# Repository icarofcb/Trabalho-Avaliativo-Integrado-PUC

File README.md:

# Trabalho-Avaliativo-Integrado-PUC
Um repositorio para o meu trabalho avaliativo integrado de eletrônica da PUC, matéria ministrada pelo professor PJ(Paulo José)

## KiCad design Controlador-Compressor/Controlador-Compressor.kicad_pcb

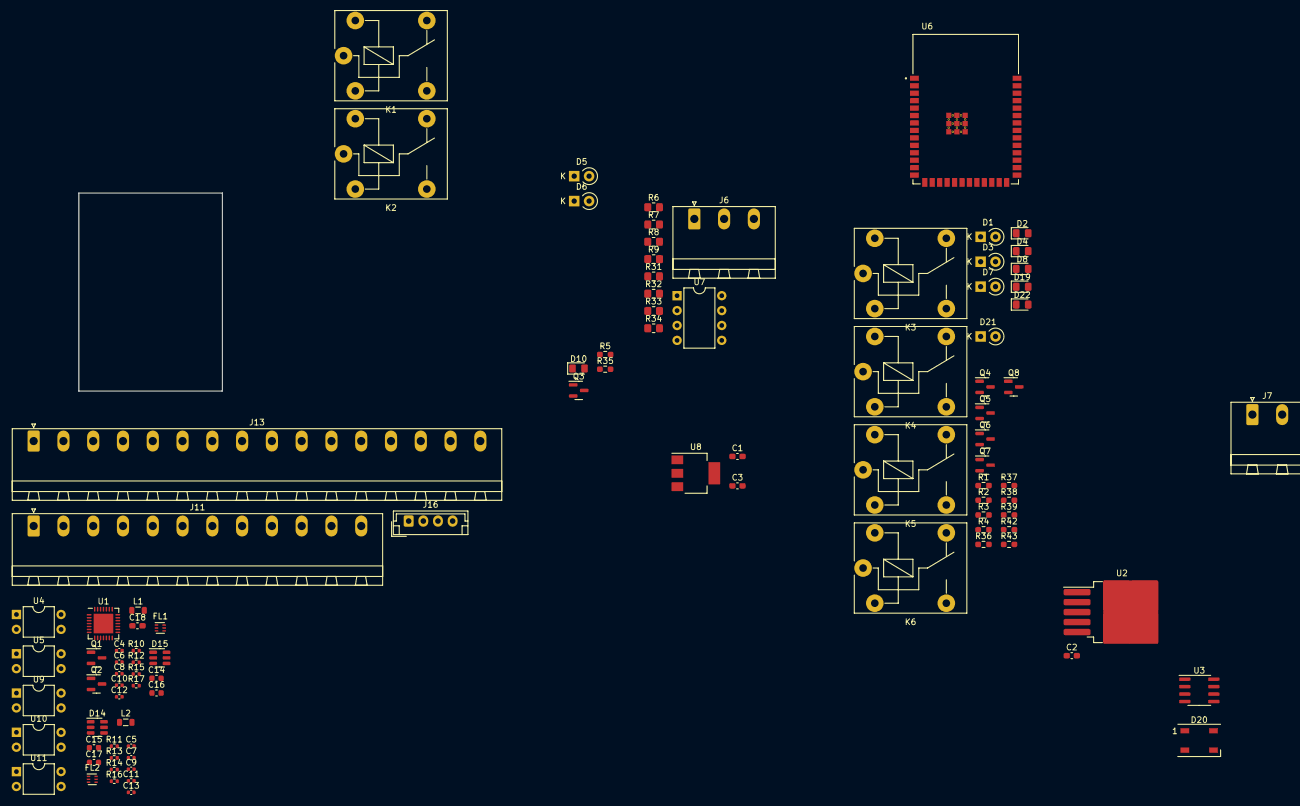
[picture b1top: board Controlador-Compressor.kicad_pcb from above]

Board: 2 copper layers, 95 parts (0 on the bottom side), 86 nets, no tracks yet.

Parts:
C1, C3, C18: 10uF; C_0603_1608Metric_Pad1.08x0.95mm_HandSolder
C2: 1uF; C_0603_1608Metric_Pad1.08x0.95mm_HandSolder
C4, C5, C8, C9: 1.5pF; C_0402_1005Metric
C6, C7, C10, C11, C12, C13: 220nF; C_0402_1005Metric
C14, C15, C16, C17: 10uF; C_0603_1608Metric
D1, D3, D5, D6, D7, D21: D; D_A-405_P2.54mm_Vertical_KathodeUp
D2, D4, D8, D10, D19, D22: LED; LED_0805_2012Metric_Pad1.15x1.40mm_HandSolder
D14, D15: SRV05-4-P-T7; SOT-23-6
D20: WS2812B; LED_WS2812B_PLCC4_5.0x5.0mm_P3.2mm
FL1, FL2: ECMF02; ST_UQFN-6L_1.5x1.7mm_Pitch0.5mm
J6: Analogico; PhoenixContact_MSTBA_2,5_3-G-5,08_1x03_P5.08mm_Horizontal
J7: Alimentação; PhoenixContact_MSTBA_2,5_2-G-5,08_1x02_P5.08mm_Horizontal
J11: Saídas Relé; PhoenixContact_MSTBA_2,5_12-G-5,08_1x12_P5.08mm_Horizontal
J13: Analógico; PhoenixContact_MSTBA_2,5_16-G-5,08_1x16_P5.08mm_Horizontal
J16: Nextion; JST_EH_B4B-EH-A_1x04_P2.50mm_Vertical
K1, K2, K3, K4, K5, K6: FINDER-36.11; Relay_SPDT_Finder_36.11
L1, L2: FBMJ2125HS420-T; L_0805_2012Metric
Q1, Q2, Q3, Q4, Q5, Q6, Q7, Q8: BC817; SOT-23
R1, R2, R3, R4, R5, R35, R36, R37, R38, R39, R42, R43: 1k; R_0603_1608Metric_Pad0.98x0.95mm_HandSolder
R6, R7: 3.3k; R_0805_2012Metric_Pad1.20x1.40mm_HandSolder
R8, R9: 10k; R_0805_2012Metric_Pad1.20x1.40mm_HandSolder
R10, R11, R12, R13: 100k; R_0402_1005Metric
R14, R15, R16, R17: 5.1K; R_0402_1005Metric
R31, R32: 33k; R_0805_2012Metric_Pad1.20x1.40mm_HandSolder
R33, R34: 100k; R_0805_2012Metric_Pad1.20x1.40mm_HandSolder
U1: CP2102N-Axx-xQFN28; QFN-28-1EP_5x5mm_P0.5mm_EP3.35x3.35mm
U2: LM2596S-5; TO-263-5_TabPin3
U3: SN75176ADR; SOIC-8_3.9x4.9mm_P1.27mm
U4, U5, U9, U10, U11: PC817; DIP-4_W7.62mm
U6: ESP32S3WROOM1N8R8; XCVR_ESP32S3WROOM1N8R8
U7: LM358; DIP-8_W7.62mm
U8: AMS1117-3.3; SOT-223-3_TabPin2

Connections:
+3V3: C2.1, C3.1, C18.1, D20.1 (VDD), U1.6 (VDD), U1.7 (VREGIN), U6.2 (3V3), U8.2 (VO)
+5V: C1.1, J16.1, U3.8 (VCC), U8.3 (VI)
+24V: D1.1 (K), D3.1 (K), D5.1 (K), D6.1 (K), D7.1 (K), D21.1 (K), J7.1, K1.A1, K2.A1, K3.A1, K4.A1, K5.A1, K6.A1, U2.1 (VIN), U7.8 (V+)
/Circuito Analógico/0_10V_FB_1: R31.2, R33.2
/Circuito Analógico/0_10V_FB_2: R32.2, R34.2
/Circuito Analógico/0_10V_OUT1: J6.1, R31.1
/Circuito Analógico/0_10V_OUT2: J6.2, R32.1
/Circuito digital/COM0: J11.2, K1.11
/Circuito digital/COM1: J11.4, K2.11
/Circuito digital/COM2: J11.6, K3.11
/Circuito digital/COM3: J11.8, K4.11
/Circuito digital/COM4: J11.10, K5.11
/Circuito digital/COM5: J11.12, K6.11
/Circuito digital/DI0: U4.4, U6.30 (IO37)
/Circuito digital/DI1: U5.4, U6.34 (IO41)
/Circuito digital/DI2: U6.35 (IO42), U9.4
/Circuito digital/DI3: U6.24 (IO47), U10.4
/Circuito digital/DI4: U6.25 (IO48), U11.4
/Circuito digital/DO0: J11.1, K1.14
/Circuito digital/DO1: J11.3, K2.14
/Circuito digital/DO2: J11.5, K3.14
/Circuito digital/DO3: J11.7, K4.14
/Circuito digital/DO4: J11.9, K5.14
/Circuito digital/DO5: J11.11, K6.14
/Circuito digital/RELE 1: R5.1, U6.19 (IO11)
/Circuito digital/RELE 2: R1.2, U6.20 (IO12)
/Circuito digital/RELE 3: R2.1, U6.21 (IO13)
/Circuito digital/RELE 4: R4.1, U6.22 (IO14)
/Circuito digital/RELE 5: R38.1, U6.8 (IO15)
/Circuito digital/RELE 6: R42.1, U6.9 (IO16)
/ESP32-S3/DE: U3.2 (~RE), U3.3 (DE), U6.29 (IO36)
/ESP32-S3/GPIO38: D20.4 (DIN), U6.31 (IO38)
/ESP32-S3/RS485_RX: U3.1 (R), U6.23 (IO21)
/ESP32-S3/RS485_TX: U3.4 (D), U6.28 (IO35)
/ESP32-S3/RX-Nextion: J16.2, U6.10 (IO17)
/ESP32-S3/RXD0: U1.25 (RXD), U6.36 (RXD0)
/ESP32-S3/TXD0: U1.26 (TXD), U6.37 (TXD0)
/ESP32-S3/Tx-Nextion: J16.3, U6.11 (IO18)
/USB->OTG/ESP_D+: D14.6 (I/O_4), FL2.1 (D+)
/USB->OTG/ESP_D-: D14.4 (I/O_3), FL2.2 (D-)
/USB->OTG/ESP_SHIELD: D14.1 (I/O_1), R11.2, R13.2
/USB->OTG/ESP_VBUS_5V: C7.1, L2.1
/USB->OTG/GPIO19: FL2.5 (D-), U6.13 (IO19)
/USB->OTG/GPIO20: FL2.6 (D+), U6.14 (IO20)
/USB->UART/D+: D15.6 (I/O_4), FL1.1 (D+)
/USB->UART/D-: D15.4 (I/O_3), FL1.2 (D-)
/USB->UART/DTR: Q2.2 (E), U1.28 (~DTR)
/USB->UART/RTS: Q1.2 (E), U1.24 (~RTS)
/USB->UART/SHIELD: D15.1 (I/O_1), R10.2, R12.2
/USB->UART/USB_D+: FL1.6 (D+), U1.4 (D+)
/USB->UART/USB_D-: FL1.5 (D-), U1.5 (D-)
/USB->UART/VBUS_5V: C6.1, D15.5 (VP), L1.1
GND: C1.2, C2.2, C3.2, C4.1, C5.1, C6.2, C7.2, C8.1, C9.1, C10.2, C11.2, C12.2, C13.2, C14.2, C15.2, C16.2, C17.2, C18.2, D14.2 (GND), D15.2 (GND), D20.3 (VSS), FL1.3 (GND), FL2.3 (GND), J6.3, J7.2, J16.4, Q3.2 (E), Q4.2 (E), Q5.2 (E), Q6.2 (E), Q7.2 (E), Q8.2 (E), R6.1, R7.1, R14.2, R15.2, R16.2, R17.2, R33.1, R34.1, U1.3 (GND), U1.29 (GND), U2.3 (GND), U2.5 (~ON/OFF), U3.5 (GND), U4.2, U4.3, U5.2, U5.3, U6.1 (GND), U6.40 (GND), U6.41_1 (GND), U6.41_2 (GND), U6.41_3 (GND), U6.41_4 (GND), U6.41_5 (GND), U6.41_6 (GND), U6.41_7 (GND), U6.41_8 (GND), U6.41_9 (GND), U7.4 (V-), U8.1 (GND), U9.2, U9.3, U10.2, U10.3, U11.2, U11.3
unnamed: C4.2, R10.1
unnamed: C5.2, R11.1
unnamed: C8.2, R12.1
unnamed: C9.2, R13.1
unnamed: D1.2 (A), D2.2 (A), K3.A2
unnamed: D2.1 (K), R3.2
unnamed: D3.2 (A), D4.2 (A), K4.A2
unnamed: D4.1 (K), R37.2
unnamed: D7.2 (A), D8.2 (A), K5.A2
unnamed: D8.1 (K), R39.2
unnamed: D5.2 (A), D10.2 (A), K1.A2
unnamed: D10.1 (K), R35.2
unnamed: D6.2 (A), D19.2 (A), K2.A2
unnamed: D19.1 (K), R36.2
unnamed: D21.2 (A), D22.2 (A), K6.A2
unnamed: D22.1 (K), R43.2
unnamed: R8.2, U7.1
unnamed: R9.2, U7.7
unnamed: Q3.1 (B), R5.2
unnamed: Q3.3 (C), R35.1
unnamed: Q4.1 (B), R1.1
unnamed: Q4.3 (C), R36.1
unnamed: Q5.1 (B), R2.2
unnamed: Q5.3 (C), R3.1
unnamed: Q6.1 (B), R4.2
unnamed: Q6.3 (C), R37.1
unnamed: Q7.1 (B), R38.2
unnamed: Q7.3 (C), R39.1
unnamed: Q8.1 (B), R42.2
unnamed: Q8.3 (C), R43.1
unnamed: R6.2, R8.1, U7.2 (-)
unnamed: R7.2, R9.1, U7.6 (-)
VBUS: C10.1, C11.1, C12.1, C13.1, C14.1, C15.1, C16.1, C17.1, L1.2, L2.2

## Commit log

2023-03-07 mei caminho andado
2023-03-08 terminei escopo do projeto
